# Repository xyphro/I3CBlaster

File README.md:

Download the I3CBlaster# I3CBlaster

## What is I3CBlaster?
I3C Blaster is a firmware image you can flash to your Raspberry PI PICO board to let it act as USB to I3C converter. Simply add 2 pullup resistors and you are ready to go.

I3CBlaster has 3 usage schemes:  
* Interactive using a terminal program like Tera-term or Putty
* From a Python program running on PC  
  To automate any tests, or building your own GUIs, ...
  A powerful feature here is, that it has an autoidentification scheme to detect the COM port number automatically. No need to struggle with which of your 20 COM ports is from the I3CBlaster device :smiley:
* Need I3C in your on RP2040 C projects? Also possible, just integrate the i3c_hl module and you are good to go!

## November 2025 update

In this Webinar I explain a bit the basics and usage of I3CBlaster. It is also a nice watch to get an introduction to I3C in general.

(click to watch)

## Right before New-Year 2025 update
HDR-DDR transfers got added :sunglasses:  
I only have V1.0 HDR-DDR capable target devices, so testing focused on that. But all aspects from V1.1 were also added. In case you start looking into HDR-DDR first time, please look into ENDXFER CCC documentation and i3c_ddr_config function, as quite some extensions were introduced in V1.1 spec version. Whenever I get access to a V1.1 capable target, I'll extend my testing.

Next planned step before doing further SW extensions is a level translator hardware and extension of the binary to the tiny <a href="https://www.seeedstudio.com/XIAO-RP2040-v1-0-p-5026.html" target="_blank">Seeedstudio Xiao RP2040 boards</a>.

## In need of an I3C Analyzer?

Have a look at my I3C daughter project, which is a Saleae Logic Analyzer plugin to decode I3C OD, I3C SDR and I3C HDR-DDR transfers:
<a href="https://github.com/xyphro/XyphroLabs-I3C-Saleae-Protocol-Analyzer" target="_blank">https://github.com/xyphro/XyphroLabs-I3C-Saleae-Protocol-Analyzer</a> 

## Do you want to decode I3C with Sigrok Pulseview?

Have a look at my I3C decoder project for Sigrok Pulseview:

<a href="https://github.com/xyphro/Sigrok-I3C-decoder" target="_blank">https://github.com/xyphro/Sigrok-I3C-decoder</a> 

### What else is this?
It is an I3C controller driver code based on a single RP2040 PIO. Feel free to reuse it in other projects!
The i3c_hl.c or .h files provide an interface to all kind of different I3C transfer types. 

To include it in your projects as a module, simply use i3c_hl.h i3c_hl.c and i3c.pio. i3c_hl.h exposes all the i3c API functions for the i3c driver. 
But don't forget credits - this project took lots of late night work to make it work well :-)

## Why did I develop I3CBlaster?
Because so far there is no easy and low $ solution available to learn I3C protocol or evaluate I3C target devices in the market.
Having the ability to execute I3C transfers was for me also a major step in understanding the I3C protocol and its many exceptions and hidden features and the reasons behind them. 

# level translator board

**[25th August 25]**

Finally i did it and added i2c functions. They are added to uart terminal, but also exposed consistently via python layer.

The new functions are:
```plaintext
  i2c_clk                  - Set I2C clock frequency
  i2c_scan                 - Scan for available i2c addreses. Reserved I2C addre
                             sses (like 0x00) are not scanned
  i2c_timeout              - Set I2C timeout value. The timeout applies to read&
                             write and the whole transfer time. The default time
                             out is 100ms
  i2c_write                - Execute an i2c write transfer to a target
  i2c_read                 - Execute an i2c read from a target
  i2c_writeread            - Execute an i2c combined write read transfer from a
                             target
```

**[1st February 25]**
I added a level translator board for the XIAO module and adjusted software to use it.
The Kicad design can be found here: <a href="https://github.com/xyphro/I3CBlaster/tree/main/hw">/hw</a>

If you want to investigate the schematic you can look here: <a href="https://raw.githubusercontent.com/xyphro/I3CBlaster/master/hw/schematic_LevelTranslatorXiaoRp2040.pdf">hw/schematic_LevelTranslatorXiaoRp2040.pdf</a>

The schematic shows also some measurement results of the board, focused on propagation delay. I am not yet happy about the propagation delays for 1.0V and 1.2V and you might need to slow down the I3C clock frequency a bit, but this is a first starting point. 

The functional supported IO voltage levels are to 0.9V 3.6V. 

The 3D case is to be released after improving the design a bit for better snap fit of the 2 halves and fixing the pinning order labels.

The edge acceleration function can be turned on and off by setting GPIO0 to either 0 (off) or to 1 (on). The gpio_write function can be used for that sake: 
* `gpio_write 0 0` to turn it off.
* `gpio_write 0 1` to turn it on (=default state).

**Software side updates:** The software auto detects now if it runs on a XIAO RP2040 board or a Raspberry pi PICO.

When running it on the Xiao module, the I3C signal pinning is:

| Module name            | SCL            | SDA            |
|----------------|----------------|----------------|
| Raspberry Pi Pico | GPIO17 | GPIO16|
| Seeed Xiao RP2040 | GPIO7 | GPIO6|

The Xiao RP2040 module has a nice NeoPixel LED. I enabled it to show in the software some states.

| LED color | Explanation |
|-----------|-------------|
|RED        | The Vtarget voltage is not supplied to the Vtarget pin | 
|GREEN      | The supplied target voltage is >= 0.9V. note that the voltage level changes "how bright" the LED will glow GREEN|
|BLUE       | Whenever data is received over the serial port, the led will flash BLUE to show activity |

## Further planned changes

Upcoming SW changes will include functional extensions, but first an instantiation method to enable running the i3c_hl module 2 I3C controllers on RP2040 on both PIO instances, but also a cleanup and Doxygen style API documentation.

## What is the difference to commercial products?

A bitbanged or here HW supported bitbanged I3C master will never get exactly to the percentage of bus utilization of a real HW I3C master.
While the implementation was targeted to be efficient here, there are phases where a PIO statemachine to CPU interaction will "pause" the bus for short times, especially for HDR-DDR transfers. The peak i3c clock frequency of 12.5MHz is reached in this solution. Have a look at the demo code section below to download a captured waveform which allows you to zoom into the timing details. Note, that those pauses are ensured to occur in phases where SCL is low, such that the I3C timings are not violated, which is important for mixed bus scenarios.

A bitbanged solution like the one here can enable you to modify its code for failure insertion to test the robustness of a target. E.g. you can send a wrong CRC value or parity on purpose, generate unexpected bus conditions, etc.

So it might not be an exact 100% replacement of commercial tools, but can be a good step for very initial tests/protocol investigation or later extension with failure insertion methods.

The USB interface is here a CDC based UART, as delivered by Raspberry PI SDK. This solution is a bit inefficient compared to a dedicated custom solution, but enables maximum usability and extendability for the community.

# What is I3C?
I3C is a successor protocol based on I2C, but enabling higher transfer rates. It pulled in many mechanisms from the less well known i2c speed modes 3.4MHz (HS), 5 MHz or 10 MHZ.
There are multiple transfer modes defined using SDR push-pull mode transfers, 2 different kinds of DDR modes are part of the public BASIC I3C specification. The full I3C specification even has multi lane support included enabling transfer rates over 100MBit/s and 2 flavors of called ternary modes where also the clock line is used to transfer data.

It maintains in a limited way compatibility to the I2C protocol. This legacy support simplifies the learning curve for new users, but creates complexity in the overall protocol definition.   
Clock stretching devices, Multi master arbitration are not supported, a maximum of  about 5 I2C devices on a single bus segment are the most dominant limitations for i2c usage on i3c busses.

It is also feasible to connect i2c and i3c devices on the same bus with limitations on max. capacitive load (50pF / 100pF) or max. datarate. Similar to i2c a degradation of the i2c clock frequency to cope with higher capacitive load is possible as function of drive strength.

Another very useful feature of I3C is the realization of the so called IBI feature: In-Band-Interrupts. I3C target devices have now the capability to raise an interrupt over the same 2 wires where it communicates with. There are 2 schemes implemented - one when the bus is busy and arbitration based scheme and another one when the bus is idle.
The IBI features is easy to understand from bus perspective, but can cause a bit of headaches for SW stacks due to out-of context occurrence within the same communication channel.

Note that according to I3C protocol definition the IBI feature only works in SDR transfer mode, so whenever HDR modes are used and an IBI feature is required ensure to transition after transfers back to SDR mode with an HDR Exit condition.

Some resources:

|Name            |Link            |
|----------------|----------------|
| Public I3C Basic spec | https://www.mipi.org/mipi-i3c-basic-download |
| A good tutorial | https://community.nxp.com/pwmxy87654/attachments/pwmxy87654/tech-days/256/1/AMF-DES-T2686.pdf |

# So: How do I get this stuff up and running?
Quite easy, follow these steps:
## Step 1: Find a Raspberry PI Pico board
Check your drawers, old projects or simply order one <a href="https://www.mouser.de/ProductDetail/Raspberry-Pi/SC0915?qs=T%252BzbugeAwjgnLi4azxXVFA%3D%3D" target="_blank">these $4 boards</a> :-)
## Step 2: Download the firmware from this repository
Enter the bin folder and download the I3CBlaster.uf2 file

## Step 3: program the firmware to RP2040
* Ensure the USB cable is not connected.
* Press and hold the BOOTSEL button on the Raspberry PI Pico board.
* Then connect the USB cable to your PC.
* Now you can release the BOOTSEL button
* Download the I3CBlaster.uf2 file from this page: <a href="https://github.com/xyphro/I3CBlaster/bin">https://github.com/xyphro/I3CBlaster/bin</a>
* A flash drive should have appeard on your PC. Drag and drop the previously downloaded I3CBlaster.uf2 file on this drive. This will start the programming. Once done, the FLASH drive removed automatically and the firmware is READY TO USE. Congrats! :-)

## Step 4: Hardware side work
Connect 2 pullup resistors from the +3.3V pin of the board to GPIO16 and GPIO17.
  
As reference: I use 2.2kOhm resistors as pullups. Other values are possible too as function of your bus capacitance and speed.

GPIO16 is the SDA line.
GPIO17 is the SCL line.

Connect an external I3C target to those lines + GND and supply.

Note, that the I3C bus operates on 3.3V IO levels. In case you want smaller IO levels you can use a device like LSF0102 or NCA9306 to translate to smaller levels.

Why did I use pullup resistors, does I3C require them?
An I3C does not need permanently enabled pullup resistors. An I3C Bus controller is keeping SCL permanently in push-pull mode and SDA will have a pullup-resistor which is enabled/disabled by the I3C controller IP on the fly at locations where the pullup is required. This maximizes power efficiency.
But this solution here will require external level translators to enable useability with external targets. The advantage of not requiring permanently enabled pullup-resistor is gone as soon as level translation is applied, because level translators cannot be protocol aware the way I3C is specified and decide autonomously if open drain or push-pull control is required. It will thus not hurt having pullup resistors enabled.
A secondary reason is, that I plan to integrate i2c functions (using RP2040 I2C IP), which will require pullup resistors to be present. 
The I3C Bus is indeed as demanded by the standard operated also in push-pull mode in SDR and DDR phases and in some phases where required in open-drain mode. 

### Now you are fully ready to go!

# Usage mode: Interactive usage using terminal program

When I3CBlaster is connected to the PC you see a COM / TTY port, simply connect to it using Putty or Tera-term. The exact baud-rate parameter/encoding settings don't matter, because this is a virtual com port.
After connecting a welcome message is shown. Press once the F1 key to help the command line interface identify the terminal emulation method. Without this e.g. the del/backspace key might behave unexpected.

Tab auto completion is supported - you can do in-line edits in your command, etc. Just like in e.g. an SSH session or command line interface.

Note that I3C Blaster supports the default Putty and Tera-term terminal emulations. It is not tested with other terminal programs and features like the in-line editing might go wrong.

Example Putty settings:

## Commands

| Command name | Description                                                                                                                                    |
|--------------|------------------------------------------------------------------------------------------------------------------------------------------------|
| help         | List all commands or give details about a specific command.<br>You can just enter help or e.g. help i3c_clk to get information about a command |
| gpio_write | Sets a gpio pin state and direction|
| gpio_read  | get gpio state. If no parameter is given a 32 Bit number containint all GPIO states is returned|
|info|Show some information about this version|
|i3c_targetreset| Execute a targetreset sequence on I3C Bus|
|i3c_drivestrength|Set the drivestrength of the controllers SDA and SCL pads. Valid values are 2, 4, 8, 12, representing 2mA, 4mA, 8mA or 12mA.
|i3c_clk|Set I3C clock frequency|
|i3c_scan|Scan for available I3C devices on the bus|
|i3c_entdaa|Execute i3c entdaa procedure. The I3C address to assign can be given as a parameter|
|i3c_rstdaa|Execute a I3C RSTDAA CCC broadcast transfer. This will un-assign all targets dynamic addresses|
|i3c_sdr_write| Execute a private write transfer to a target|
|i3c_sdr_read | Execute a private read from a target|
|i3c_sdr_writeread | Execute a private combined write read transfer from a target. Useful e.g. to read register values|
|i3c_sdr_ccc_bc_write| Execute a ccc broadcast write transfer|
|i3c_sdr_ccc_direct_write|Execute a ccc direct write transfer|
|i3c_sdr_ccc_direct_read|Execute a ccc direct read transfer|
|i3c_poll|Allows a readout of IBI or HJ (hotjoin) information from the bus. Call this function in case an IBI was signalled back when calling a transfer function or in regular intervals to ensure you get to see IBIs|
|i3c_ddr_config|Configure I3C behavior/ I3C target capability. Look into ENDXFER CCC for complete explanation|
|i3c_ddr_write|Execute a private DDR mode write transfer to a target. The function returns error code and how many words have actually been written|
|i3c_ddr_read|Execute a HDR-DDR mode read transfer from a target. The function returns error code and the read data words|
|i3c_ddr_writeread|Execute a HDR-DDR mode write transfer followed by a read. The function returns error code and how many words have actually been written and read data words|

Each command parameters can be seen when typing:
<br>help [functionname]
<br>so e.g. help i3c_sdr_write
<br>in the console

Each I3C command returns a single line response returning an error code and optionally data.

```plaintext
> i3c_entdaa 0x30
OK(0),0x04,0x6a,0x00,0x00,0x00,0x00,0x27,0xa0
```
OK(0) is the error code. There is always a text followed by a error number in brackets. 0 means: no error.
The rest of the response shown above is data received during the entdaa process (e.g. BCR)

## Example interactive usage:

Reset any previously assigned dynamic address assignment:
```plaintext
> i3c_rstdaa
OK(0)
```
Now assign a dynamic address 0x30 to a connected i3c devices:
```plaintext
> i3c_entdaa 0x30
OK(0),0x04,0x6a,0x00,0x00,0x00,0x00,0x27,0xa0
```

Now scan the i3c bus for available i3c addresses:
```plaintext
> i3c_scan
OK(0),0x30,0x7e
```
As we can see the device is detected on address 0x30 and also the broadcast address 0x7E.

Now we can execute a transfer:
In this case we write 2 bytes to the i3c device: 0x00 and 0x00 followed by a request to read 8 bytes.
```plaintext
> i3c_sdr_writeread 0x30 0x00,0x00 8
OK(0),0x00,0x01
```
The transfer was successful ("OK(0)") and 2 bytes were read. This is, because the device stopped the transfer after 2 bytes of reading. So also this is correctly handled by the I3cBlaster.

# Usage mode: Python

To be able to talk with I3CBlaster from Python I created a Python module.

This enables YOU to create automated testcases or even create GUI applications to use I3CBlaster with it.

The Python mode uses the same command line interface, but enables a special operation mode in it by starting each command with a '@' letter. This letter turns off the ECHO done by the command line interface when entering commands to get a bit more efficiency.

This module is done with the intention to be EASY useable. This e.g. involves also that I don't want you to struggle finding the right COM/TTY port number -> The COM port is identified automatically.
Disclaimer: I did only test this under Windows, but it should work flawless under Linux too. Have to test this during next days once on my linux machine, but since a few weeks I am in a Windows mode (*Yes, shame on me!*).

The python module but also an example code is located in the python subdirectory. It should be pretty self explaining and exposes the same commands as the interactive mode.

The file i3cblaster_demo_runme.py is a python code using the i3cblaster module.
i3cblaster.py contains the code of the i3cblaster module itself.

But to show how easy it is to use the API and entertain your curiosity quickly, here an example code:
```python
import i3cblaster

# list available and connected i3c blaster devices:
devices = i3cblaster.listdevices() # this returns an array with serial numbers of connected i3cblaster devices
print(len(devices), ' i3cblaster devices connected:', devices)

if len(devices) > 0:
    i3c = i3cblaster.i3cblaster() # in case multiple devices are connected you can provide the serial number here as a parameter
    
    print('resetting dynamic addresses previously assigned')
    i3c.i3c_rstdaa()

    print('scanning for available i3c devices')
    targets = i3c.i3c_scan()
    print('found target devices on bus:', targets)
    
    print('assign a dynamic address - this only works for i3c devices supporting it, but will not cause issues')
    i3c.i3c_entdaa(0x30)
    
    print('scanning for available i3c devices')
    targets = i3c.i3c_scan()
    print('found target devices on bus:', targets)
    
    print('reading up to 10 bytes from subregister 0x00:')
    data = i3c.i3c_sdr_writeread(0x30, [0x00], 10)
    print('result: ', data)

    print('Setting controllers SDA/SCL drivestrength to 4mA')
    data = i3c.i3c_drivestrength(4)
    print('result: ', data)
    
    print('Executing a HDR-DDR Write')
    i3c.i3c_ddr_write(0x30, 0x00, [0x1234, 0x5678])

    print('Executing a HDR-DDR Read')
    data = i3c.i3c_ddr_read(0x30, 0x00, 10)
    print('result: ', data)

    print('Executing a HDR-DDR Write followed by read')
    data = i3c.i3c_ddr_writeread(0x30, 0x00, 0x00, [0x1234, 0x5678], 10)
    print('result: ', data)
```

I captured the SDA and SCL line using my Saleae logic analyzer - in case you are curious about the timing of this solution. It includes all above phases, so also the newly added DDR phases: <a href="https://raw.githubusercontent.com/xyphro/I3CBlaster/master/pictures/Example_trace_from_demo_runme_pythonscript.sal" target="_blank">Example_trace_from_demo_runme_pythonscript.sal</a>

# Finally: The good to knows

The i3c_hl implementation using PIO is supporting the i3c address phase arbitration scheme.

A transfer will always start with an arbitration header written in Open Drain mode. This is the only flexible method which supports all I3C environments. Why? Think about a device wants to raise an IBI and does that at a point of time where a private read to the same I3C device is executed: The controller is not capable to differentiate in that case between if an IBI with payload was received or the actual read data. For limited well known environments I3C allows also tweaked performance optimized addressing phases, but here I did not support them for the reason of flexibility.

Although you see 2 pullup resistors have to be added, the lines get driven in push-pull mode during SDR phases.
I3C does not require a pullup on the SCL line as it is driven by the master in push-pull mode, still I add here one. Why? Because I2C functions will get added to this too soon and I2C requires a pullup resistor.

Something very important to know on I3C protocol is that the ACK phase is different to I2C ACK. On I2C only the state of the line during HIGH phase is used for acknowledgment information. On I3C the ACK - although it looks very similar does signal if "more bytes can be transferred" and the Controller can signal also back if it want to continue transfering more data bytes.

# Signal integrity

During experimentation while enabling HDR-DDR transfers it turned out that signal integrity is much more critical for DDR mode transfers compared to SDR mode.

Due to this I introduced an option to set the drive strength.

Items which affect the integrity a lot are:
* Controller drive strength on SDA and SCL
* Target drive strength - many targets have the ability to set the drive strength with an SDR transfer
* Good ground connection between controller and target to avoid ground bounce. I have seen agressive high frequency ground bounce of e.g. up to +-1V when just wiring controller and target together with just a single Dupont jumper wire. This high number was also partly caused by the targets high slew rate before reconfiguring it.
* Other topics like minimizing trace length, minimize capacitive coupling with layout techniques.

All this does not mean, that you cannot wire a target to the controller with normal jumper wire, but it might create issues and you need to look into signal integrity.
If you see issues like CRC or parity errors, consider looking with an oscilloscope at SDA and SCL signal. Ideally do this with high impedance active differential probes. Use peak-detect acquisition decimation mode, rather than high-res or sample to ensure, that short peaks are really visible.

Here an example of "bad" SDA/SCL signals measured with an active high impedance differential probe:

The target was here wired with 4 jumper wires from RP2040 to the I3C target: GND, VCC, SDA and SCL.
The SDA signal is driven by the target during the visible phase. The controller side driving phases of the SDA signal are much better behaved.

Apart of the SCL line showing (minor) ringing, the SDA line shows very strong ringing caused by a very high slew-rate and wiring inductive components. More investigations have shown, that ground bouncing due to having just a single thin jumper wire for GND contributed also a lot to it.
You can also see a strong coupling from SDA to SCL, which creates an implicit unwanted clock edge on SCL. This caused HDR-DDR transfers to be not working correctly.

After optimizing this by connecting the target directly to the RP2040 with just a female pinheader it got majorly improved:

(Note: The signal content is different, because the improvements rendered I3C transfers to a working state)

There are in practice of course a lot more aspects to signal integrity, e.g. capacitive load, length of lines (aka inductance, cross-talk), termination, source and sink impedance... But I want to give this just as some first pragmatic experience here without going into the depths. A good presentation with a much more sophisticated view of I3C signal integrity in certain applications can be found here: <a href="https://www.youtube.com/watch?v=Ju-UhFAgRLg" target="_blank">https://www.youtube.com/watch?v=Ju-UhFAgRLg</a>

**Pull requests or seeing modifications of this is very welcome!**

What about e.g. making a Micropython module out of it? this would add a lot of value and I'd love to see that coming.

*(Update 3rd November 2024: I started looking into it and it seems very feasible to create a .MPY module which can be imported like a normal python module. The difficulty lies into combining the MakeFile based system with the CMAKE based PICO SDK build. This will also likely be the case we don't see that many .MPY modules for RP2040. A bit more complex Frankenstein approach has to be me made... But I'll look into it further).*

**In case of feedback/questions -> See discussion section or for problems: File a ticket in issues section!**

But note: I won't be able to respond always immediately, ... Sometimes it can be within hours, sometimes days or months. I don't make a living out of this and simply want to increase the amount of i3c tools available to the public. Consider this a community project and try to help yourself also - the full source code is included in this repository.

# How to compile yourself

There is no need to compile anything, if you just want to use it as is. But in case you want to make changes/extensions:

The project is setup to work without pico SDK being installed. You only need to have a VSCode installation with arm-none-eabi toolchain and CMAKE. After configuring CMAKE you the picosdk is downloaded during first build. After any further builds the presence of picosdk is detected and no further buildtime gets wasted.

In case you reuse in your own projects, please give visible credits according to the MIT license.

**So: Have fun using it!**

# Ending words

Disclaimer: Use at your own risk. I am not guilty for any negative effect like broken hardware or dataloss. Also: No animals were harmed during creation of this.
I3C is a trademark of MIPI Aliance, MIPI is a trademark of MIPI Aliance. 
This development is done by an individual contributor and not done by or related to MIPI Aliance.

In case MIPI Aliance is not OK that I use the I3C term here contact me under "xyphro at gmail.com" and I rename it to something else following what has been done with I2C for many years resulting in "style flower analogously" like TWI (two wire interface) or others.

Project home address: <a href="https://github.com/xyphro/I3CBlaster">https://github.com/xyphro/I3CBlaster</a>

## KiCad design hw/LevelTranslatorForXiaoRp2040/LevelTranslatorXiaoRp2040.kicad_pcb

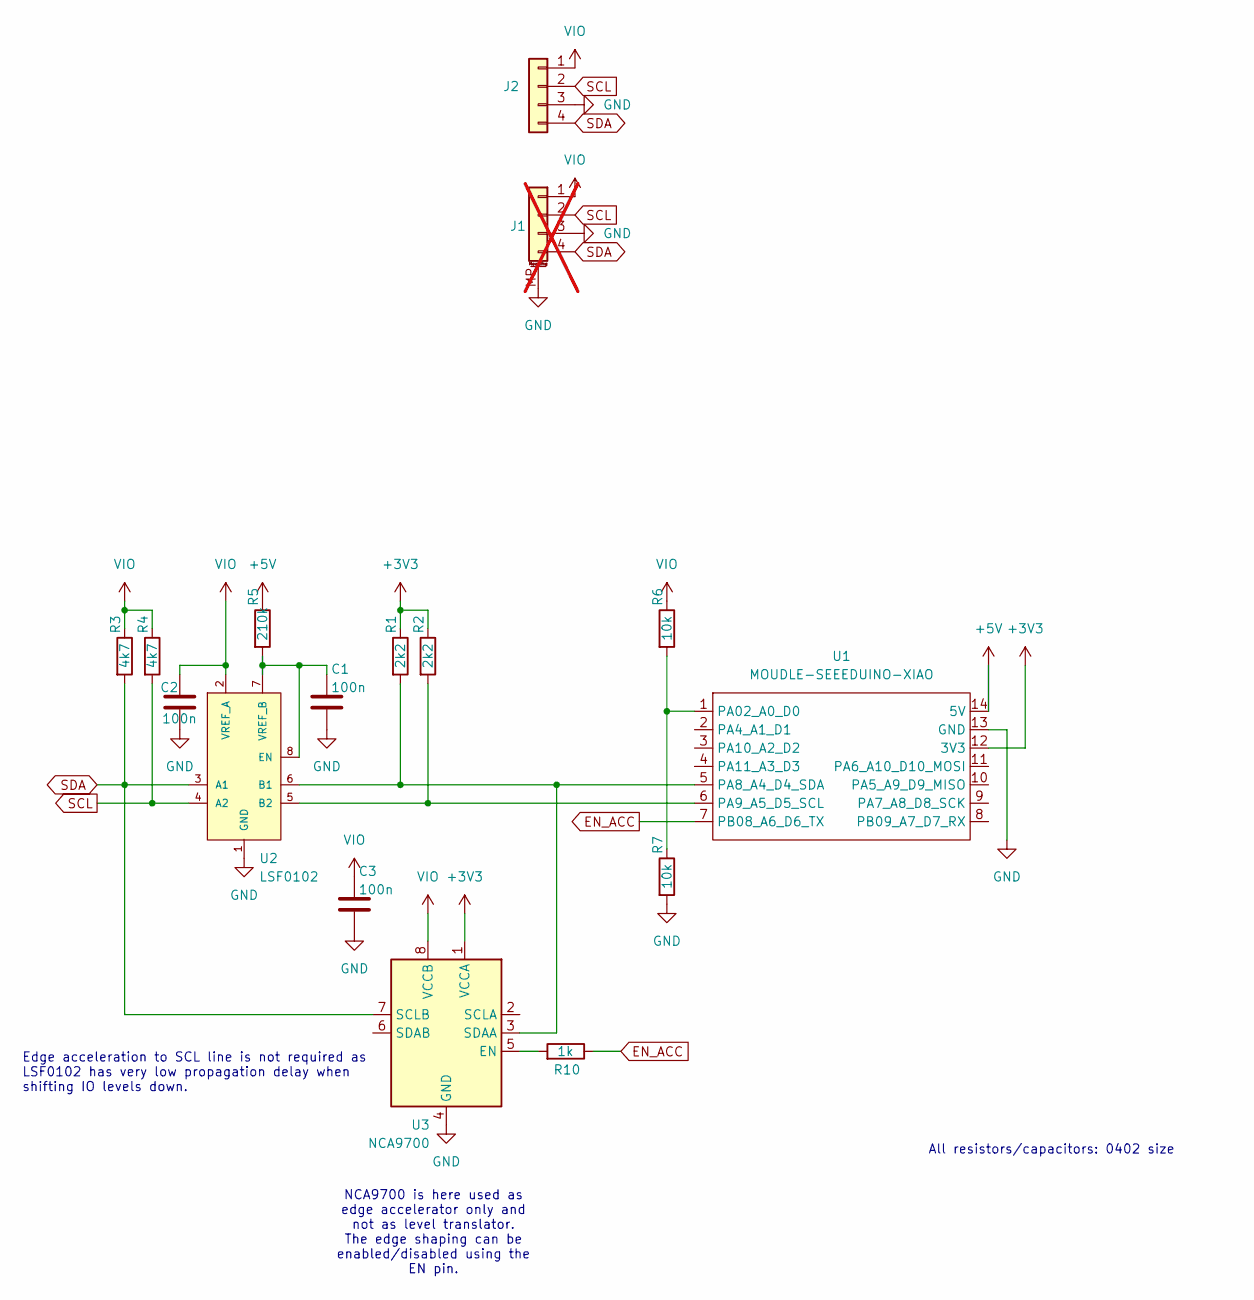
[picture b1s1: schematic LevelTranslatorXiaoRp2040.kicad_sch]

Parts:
C1, C2, C3: 100n; C_0402_1005Metric
J1: Conn_01x04_MountingPin; JST_ACH_BM04B-ACHSS-A-GAN-ETF_1x04-1MP_P1.20mm_Vertical; not fitted
J2: Conn_01x04; PinHeader_1x04_P2.54mm_Vertical
R1, R2: 2k2; R_0402_1005Metric
R3, R4: 4k7; R_0402_1005Metric
R5: 210k; R_0402_1005Metric
R6, R7: 10k; R_0402_1005Metric
R10: 1k; R_0402_1005Metric
U1: MOUDLE-SEEEDUINO-XIAO; MOUDLE14P-SMD-2.54-21X17.8MM
U2: LSF0102; SOP50P310X90-8N
U3: NCA9700; VSSOP-8_3.0x3.0mm_P0.65mm

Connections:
+3V3: R1.1, R2.1, U1.12 (3V3), U3.1 (VCCA)
+5V: R5.1, U1.14 (5V)
EN_ACC: R10.1, U1.7 (PB08_A6_D6_TX)
GND: C1.2, C2.2, C3.2, J1.3, J1.MP (MountPin), J2.3, R7.2, U1.13 (GND), U2.1 (GND), U3.4 (GND)
unnamed: R6.2, R7.1, U1.1 (PA02_A0_D0)
unnamed: R1.2, U1.5 (PA8_A4_D4_SDA), U2.6 (B1), U3.3 (SDAA)
unnamed: R2.2, U1.6 (PA9_A5_D5_SCL), U2.5 (B2)
unnamed: C1.1, R5.2, U2.7 (VREF_B), U2.8 (EN)
unnamed: R10.2, U3.5 (EN)
SCL: J1.2, J2.2, R4.2, U2.4 (A2)
SDA: J1.4, J2.4, R3.2, U2.3 (A1), U3.7 (SCLB)
VIO: C2.1, C3.1, J1.1, J2.1, R3.1, R4.1, R6.1, U2.2 (VREF_A), U3.8 (VCCB)

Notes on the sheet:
Edge acceleration to SCL line is not required as LSF0102 has very low propagation delay when shifting IO levels down.
All resistors/capacitors: 0402 size
NCA9700 is here used as edge accelerator only and not as level translator. The edge shaping can be enabled/disabled using the EN pin.

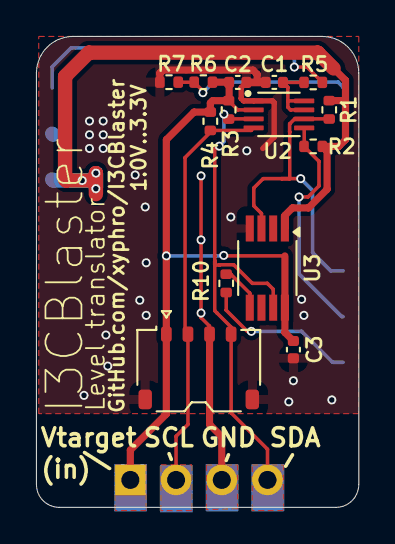
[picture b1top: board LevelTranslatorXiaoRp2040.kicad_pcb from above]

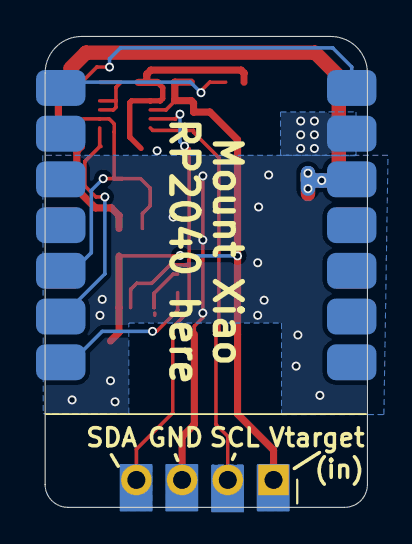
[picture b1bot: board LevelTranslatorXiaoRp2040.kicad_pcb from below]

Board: 2 copper layers, 17.9 x 26.2 mm, 16 parts (2 on the bottom side), 12 nets.

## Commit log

2024-11-01 First commit
    Hello World!
2024-11-01 Update README.md
    Fix picture links
2024-11-01 Update README.md
    fix some of the worst typos.
2024-11-01 some more fixes
2024-11-01 Create i3cblaster.uf2
    Forgot to commit the binary firmware image. So here it is :-)
2024-11-03 Update README.md
    fix some typo / extend description
2024-11-10 add config.yml for google indexing
2024-12-31 Extensions with HDR-DDR mode functions, adding drive strength function
2024-12-31 missed adding those changes in last commit
2024-12-31 just some text changes/fixes
    yes there are still some typos, but I am blind for today. Need to check on another day again :-)
2025-01-03 Adding an outlook to level translator and update readme.md structure a bit
2025-01-03 smaller updates to README.md
2025-01-12 add housing picture
2025-02-01 Added supported for Xiao RP2040 module & share level translator board design
2025-02-01 fix some links
2025-02-01 Add explanation on how to turn edge shaping on and off
2025-06-22 add link to Sigrok pulseview MIPI I3C decoder
2025-08-24 integrated i2c functions
    Finally done something I wanted to do since long time - I added I2C functionality:
    New functions: i2c_clk, i2c_timeout, i2c_write, i2c_read, i2c_writeread. All integrated in terminal, but also python layer , have fun :-)
2025-10-25 Fix ccc bc and direct write python implementation
    It was fine in the C and terminal usage mode.
2025-11-01 inserted link to Elektor/Mipi Webinar
2025-11-02 Fix Gerber output
    R8/R9 in previous version are "do not mount"
2026-06-25 some bugfixes from plugfest
    - I3C fix: When a during a read a target requested an abort of the transfer during Bit 9 phase, the controller did not properly confirm it
    - fixed an issue in i3c_scan - sometimes it did abort scanning before trying out all i3c addresses
    - ported to latest pio SDK
2026-06-25 add version string to 'info' and welcome message
    Try to derive a version string from git and show it when running
    I3CBlaster for easier references.
2026-06-25 update binary after merging the version_string enhancement
    Contains 'initial-36-g596a6e1' as version

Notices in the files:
README.md:
In case you reuse in your own projects, please give visible credits according to the MIT license.
